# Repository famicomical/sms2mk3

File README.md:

# sms2mk3

Play your US Sega Master System games on a Japanese console. 
The compact design of this board reduces its cost and allows for more flexibility in mounting compared to other options on the market.

The sms2mk3 has the correct vertical size to fit inside a Sega Mark III or Japanese SMS cartridge. It was initially designed to re-use a Japanese Mark III cartridge as housing for a first-generation (legacy) Krikzz Master Everdrive. The design has been tested and confirmed to work for this use case.

Due to the recessed backs of these cartrdiges, case cutting may be necessary to fit the cartrdige slot. Alternatively, you can use the quick-solder board to permanently affix your US cartridge to the converter board, and you will be able to fit it all inside a Japanese Sega cartridge without external case cuts.

## Future goals

This project would most effectively be used with a newly manufactured plastic shell which has had its mounting extrusions correctly aligned with the screw holes on a US Master System game PCB. This would allow for a direct fit of the game and converter PCB assembly inside the housing. i haven't attempted 3D modeling the shell yet.

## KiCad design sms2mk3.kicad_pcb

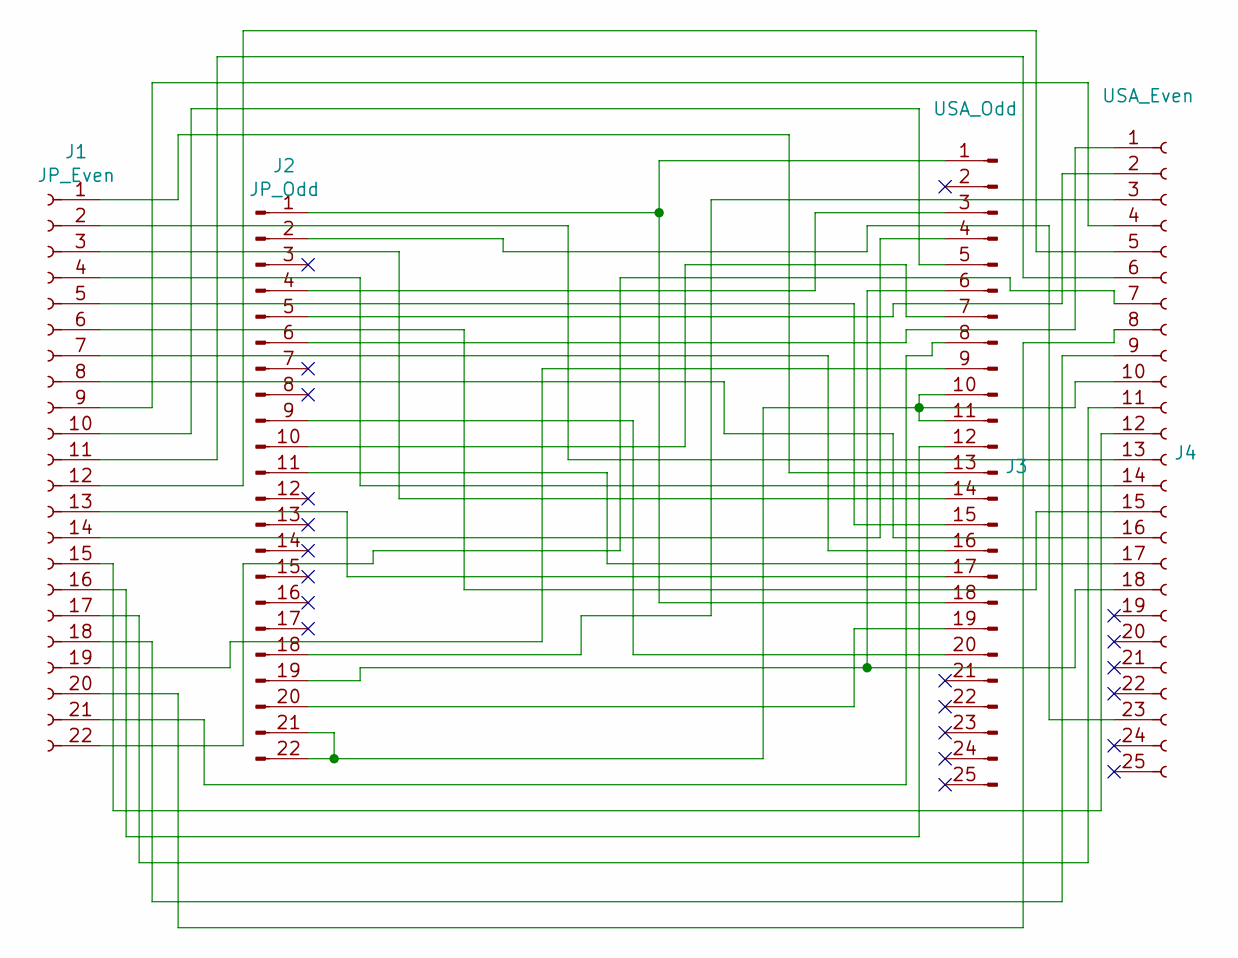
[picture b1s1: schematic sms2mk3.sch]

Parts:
J1: JP_Even; JP_SMS
J2: JP_Odd; JP_SMS
J3: USA_Odd; US_SMS
J4: USA_Even; US_SMS

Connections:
unnamed: J1.1, J3.13
unnamed: J1.2, J4.13
unnamed: J1.3, J3.14
unnamed: J1.4, J4.14
unnamed: J1.5, J3.15
unnamed: J1.6, J4.15
unnamed: J1.7, J3.16
unnamed: J1.8, J4.16
unnamed: J1.9, J4.4
unnamed: J1.10, J3.5
unnamed: J1.11, J4.6
unnamed: J1.12, J4.5
unnamed: J1.13, J3.17
unnamed: J1.14, J3.4
unnamed: J1.15, J4.12
unnamed: J1.16, J3.12
unnamed: J1.17, J4.11
unnamed: J1.18, J4.9
unnamed: J1.19, J3.9
unnamed: J1.20, J4.8
unnamed: J1.21, J3.8
unnamed: J1.22, J4.7
unnamed: J2.1, J3.1, J3.18
unnamed: J2.2, J4.23
unnamed: J2.4, J3.3
unnamed: J2.5, J4.2
unnamed: J2.6, J4.1
unnamed: J2.9, J3.20
unnamed: J2.10, J3.7
unnamed: J2.11, J4.17
unnamed: J2.18, J4.3
unnamed: J2.19, J3.6, J4.18
unnamed: J2.20, J3.19
unnamed: J2.21, J2.22, J3.10, J3.11, J4.10

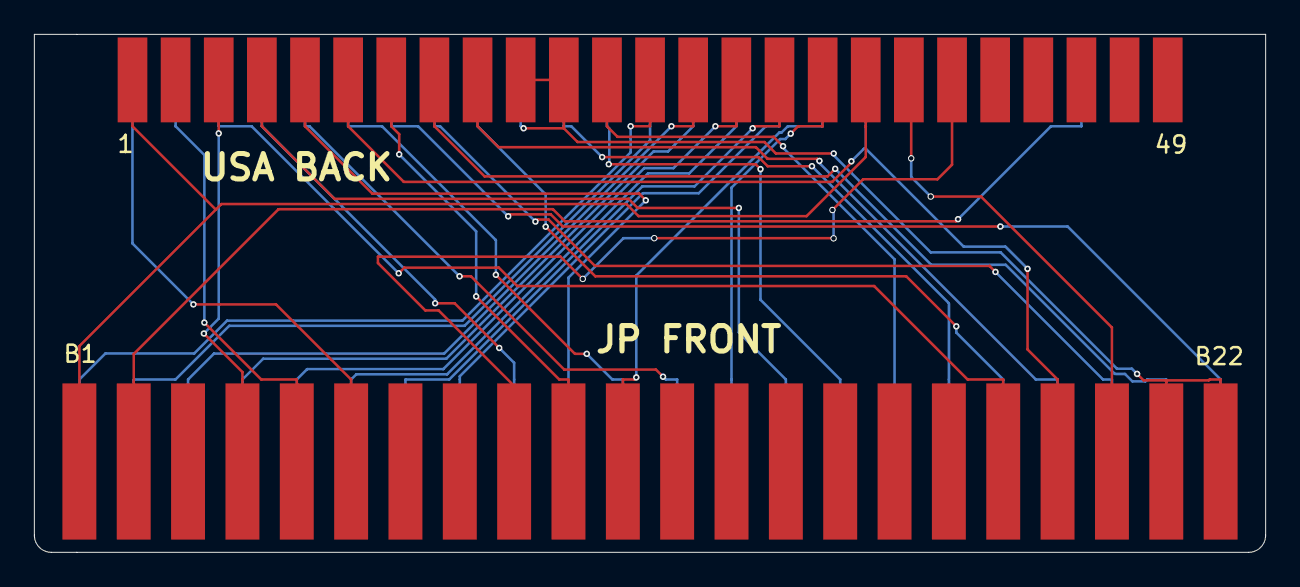
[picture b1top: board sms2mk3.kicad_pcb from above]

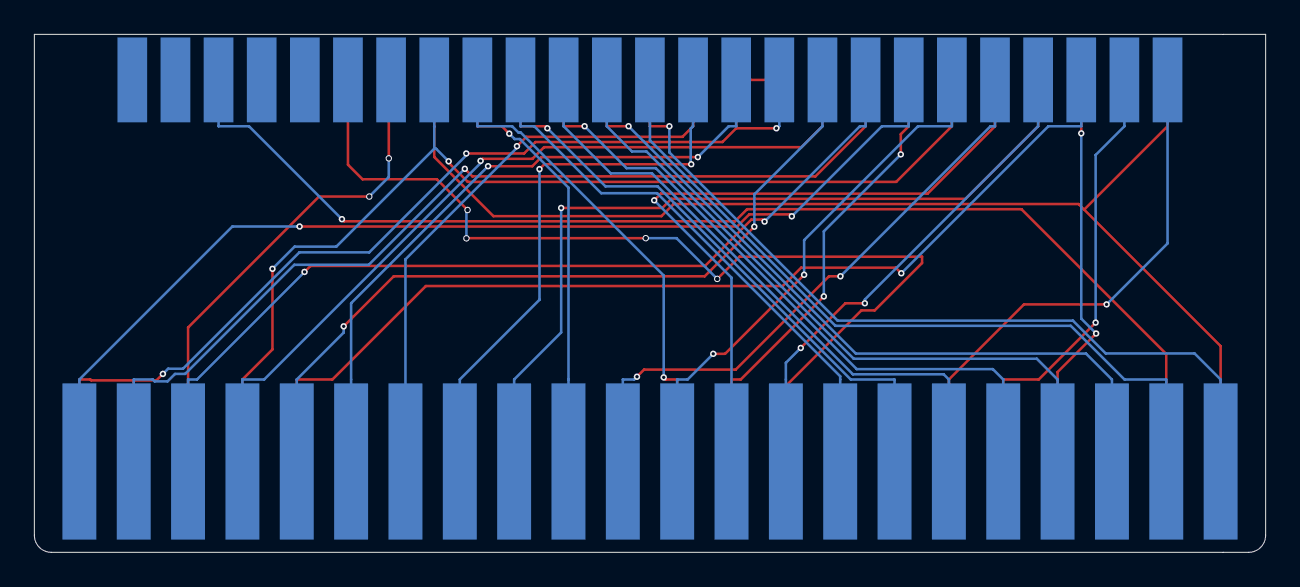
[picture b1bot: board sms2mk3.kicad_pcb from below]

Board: 2 copper layers, 72.5 x 30.5 mm, 4 parts (2 on the bottom side), 34 nets.

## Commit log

2023-03-16 rename
2023-03-16 add QSB
2023-03-16 add figures
